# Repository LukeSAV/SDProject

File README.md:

# **SDProject**

Repo for senior design code

Link to project video: https://www.youtube.com/watch?v=O6JMgqfRybo&t=1s

## <u>Matlab</u>

Contains matlab test harness and associated files for the Extended Kalman Filter - This has since been converted to ekf_node in the ROS workspace.

## <u>SDMicro</u>

Contains all microcontroller related code for the project.

## <u>boards</u>

Contains files related to PCB design and schematics.

## <u>iOS</u>

This contains all project files related to XCode and iOS. 

##### /D2U

DeliveryInformation.swift - Singleton class used to hold relevant information to the delivery in progress.

DeliverySettingsController.swift - ViewController for the settings page. Formats and periodically updates the information on the page from FireBase.

MapMainController.swift - ViewController for the main map page. Handles map centering on desired user location and updates respective UI elements.

Waypoint.swift - Inherits MKPointAnnotation to apply color to dropped pins to distinguish between types.

## <u>ros_ws</u>

This is the ROS workspace for the project. Any packages/nodes made in ROS should be located here.

#### ROS Packages:

##### fb

This package contains the fb_node that handles interfacing to firebase. 

Nodes:

- fb_node: 
  - Publishes - /delivery_requested_status (Type: Bool)
  - Subscribes - /rtk_gpgga (Type: String)

##### rtk

This package contains the rtk_gps_node that runs code to support RTK corrections for the NS-HP-GL GPS/GNSS device. 

Nodes:

- rtk_gps_node
  - Publishes - /rtk_gpgga (Type: NavSatFix), /rtk_gpvtg (Type: HeadingSpeed)
  - Subscribes - None

##### rtk_controller

This package contains the rtk_controller node that performs path point generation to send to the microcontroller. A* algorithm, path point projection, and much more.

Nodes:

- rtk_controller_node
  - Publishes - /robot_cmd (Type: String), /next_waypoint (Type: NavSatFix), /goal_pt (Type: NavSatFix), /goal_math_pt (Type: NavSatFix)
  - Subscribes - /ekf/filtered (Type: NavSatFix), /ekf/imu/data (Type: Imu), /rtk_gpvtg (Type: String), /perception/map (Type: Image), /pitch (Type: Float32) 

##### joystick_drivers

This package contains the joy_node that interfaces the PS4 controller to ROS.

Nodes:

- joy_node: 
  - Publishes - /joy (Type: Joy)
  - Subscribes - None 

##### serial

This package contains the serial_node that handles all communication with the microcontroller.

Nodes:

- serial_node:
  - Publishes - /encoder (Type: String), /goal_string (Type: String)
  - Subscribes - /joy (Type: Joy), /delivery_requested_status (Type: Bool), /robot_cmd (Type: String)

##### perception

This package contains the lidar_node that handles creation of an obstacle map that the path planning algorithm may be run on.

Nodes:
- lidar_node:
  - Publishes - /perception/map (Type: Image)
  - Subscribes - /scan_img (Type: Image)
  
##### ekf

This package contains the ekf_node that runs the Extended Kalman Filter to fuse the robot sensor information.

Nodes:
- ekf_node:
  - Publishes - /ekf/filtered (Type: NavSatFix), /ekf/imu/data (Type: NavSatFix), /pitch (Type: Float32)
  - Subscribes - /imu/data (Type: Imu), /rtk_gpgga (Type: NavSatFix), /encoder (Type: String)

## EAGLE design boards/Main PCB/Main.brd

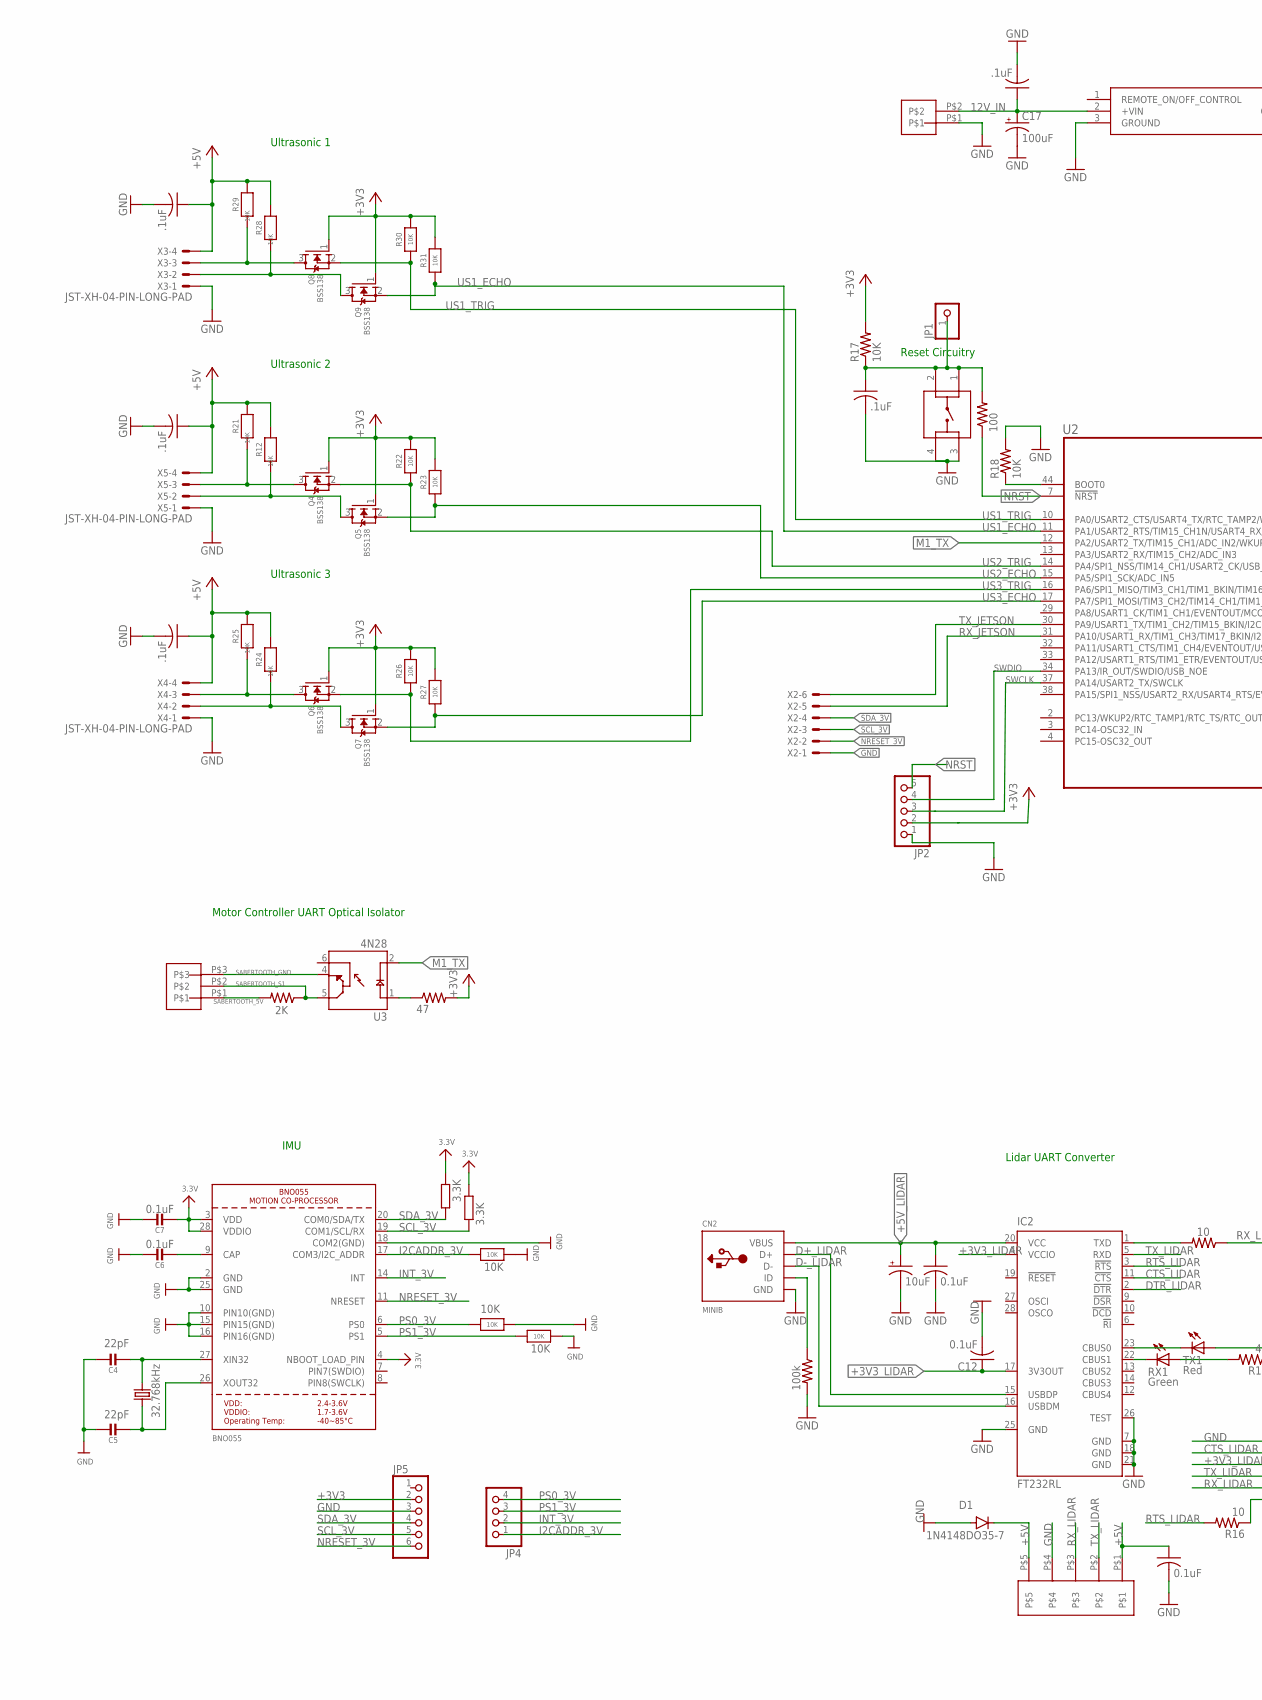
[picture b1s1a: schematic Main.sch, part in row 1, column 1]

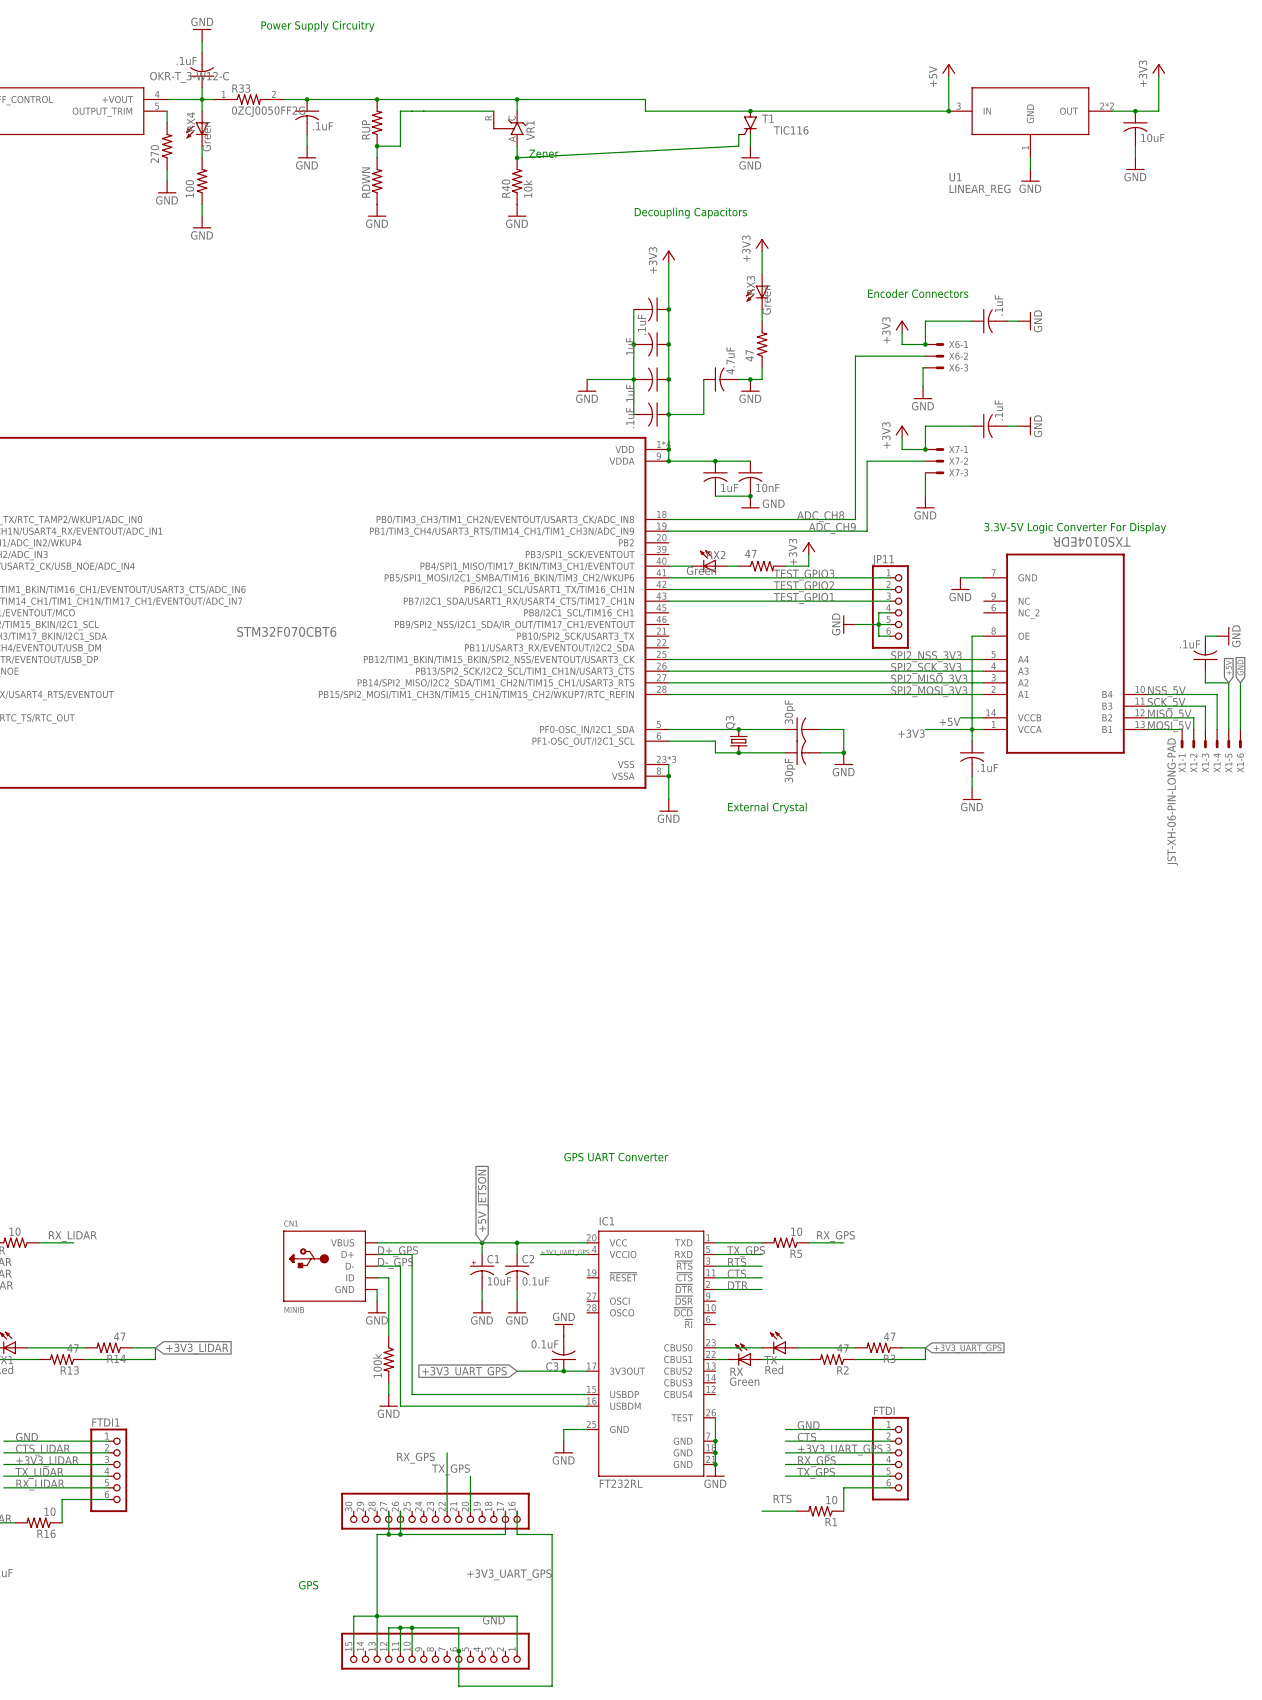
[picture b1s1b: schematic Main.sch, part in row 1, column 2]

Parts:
C1, C10: 10uF; A/3216-18R
C2, C3, C11, C12, C30: 0.1uF; C0805K
C4, C5: 22pF; 0805-NO
C6: 0.1uF; 0805-NO
C7: 0.1uF; 0805_10MGAP
C8, C13, C18, C19, C22, C23, C24, C25, C26, C27, C28, C29, C31, C32, C33: .1uF; C0805
C9: 10uF; C0805
C14, C15: 30pF; C0805
C16: 4.7uF; C0805
C17: 100uF; E2,5-7
C20: 1uF; C0805
C21: 10nF; C0805
CN1, CN2: MINIB; USB-MINIB
D1: 1N4148DO35-7; DO35-7
FTDI, FTDI1: PINHD-1X6CB; 1X06-CLEANBIG
IC1, IC2: FT232RL; SSOP28
IC4: OKR-T_3-W12-C; MURATACASEC72
J1: 3_PIN_JST-XH
J2: 2_PIN_JST-XH
J3: 5_PIN_JST-XH
JP1: PINHD-1X1; 1X01
JP2: PINHD-1X5; 1X05
JP4: HEADER-1X476MIL; 1X04_ROUND_76
JP5: MICROBUILDER_HEADER-1X676MIL; MICROBUILDER_1X06_ROUND_76
JP11: PINHD-1X6; 1X06
Q3: CRYSTALHC49S; HC49/S
Q4, Q5, Q6, Q7, Q8, Q9: BSS138; SOT23-WIDE
R1, R5, R15, R16: 10; R0805
R2, R3, R10, R11, R13, R14, R19: 47; R0805
R4, R6, R7, R22, R23, R26, R27, R30, R31: 10K; 0805-NO
R8, R9: 3.3K; R0805
R12, R21, R24, R25, R28, R29: 10K; _0805MP
R17, R18: 10K; R0805
R20: 2K; R0805
R32, R37: 100; R0805
R33: 0ZCJ0050FF2G; RESC3216X125N
R34, R35: 100k; R0805
R36: 270; R0805
R40: 10k; R0805
RDWN: R-US_R0805; R0805
RESET: TACTILE_SWITCH; SW_1825910-6-4
RUP: R-US_R0805; R0805
RX, RX1, RX2, RX3, RX4: Green; CHIP-LED0805
T1: TIC116; TO220CS
TX, TX1: Red; CHIP-LED0805
U1: LINEAR_REG; SOT223
U2: STM32F070CBT6; QFP50P900X900X160-48N
U3: 4N28; DIP880W50P254L780H450Q6
U4: TXS0104EDR; SOIC127P600X175-14N
U$1: GPS
U$3: BNO055
VR1: TL431CLP; TO92-CLP
X1, X2: JST-XH-06-PIN-LONG-PAD; JST-XH-06-PACKAGE-LONG-PAD
X3, X4, X5: JST-XH-04-PIN-LONG-PAD; JST-XH-04-PACKAGE-LONG-PAD
X6, X7: JST-XH-03-PIN-LONG-PAD; JST-XH-03-PACKAGE-LONG-PAD
Y1: 32.768kHz; CRYSTAL_8X3.8

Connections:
12V_IN: C17.+, C32.1, IC4.2 (+VIN), J2.P$2
+3V3: C7.2, C9.1, C16.1, C20.1, C21.1, C22.1, C23.1, C24.1, C25.1, C28.1, C29.1, C33.1, JP2.2, JP5.2, Q4.1 (G), Q5.1 (G), Q6.1 (G), Q7.1 (G), Q8.1 (G), Q9.1 (G), R8.2, R9.2, R10.2, R17.2, R19.2, R22.2, R23.2, R26.2, R27.2, R30.2, R31.2, RX3.A, U1.2 (OUT), U1.4 (OUT), U2.1 (VDD), U2.9 (VDDA), U2.24 (VDD), U2.36 (VDD), U2.48 (VDD), U4.1 (VCCA), U4.8 (OE), U$3.3 (VDD), U$3.4 (NBOOT_LOAD_PIN), U$3.28 (VDDIO), X6.1, X7.1; also elsewhere on the board
+3V3_LIDAR: C12.1, FTDI1.3, IC2.4 (VCCIO), IC2.17 (3V3OUT), R13.1, R14.1
+3V3_UART_GPS: C3.1, FTDI.3, IC1.4 (VCCIO), IC1.17 (3V3OUT), R2.1, R3.1, U$1.6, U$1.10, U$1.11, U$1.12, U$1.16 (1)
+5V: C8.1, C18.1, C19.1, C26.1, C27.1, C30.1, D1.C, J3.P$1, J3.P$5, R12.2, R21.2, R24.2, R25.2, R28.2, R29.2, R33.2, RUP.2, T1.A, U1.3 (IN), U4.14 (VCCB), VR1.C, X1.5, X3.4, X4.4, X5.4
+5V_JETSON: C1.+, C2.1, CN1.VBUS, IC1.20 (VCC)
+5V_LIDAR: C10.+, C11.1, CN2.VBUS, IC2.20 (VCC)
ADC_CH8: U2.18 (PB0/TIM3_CH3/TIM1_CH2N/EVENTOUT/USART3_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), X6.2
ADC_CH9: U2.19 (PB1/TIM3_CH4/USART3_RTS/TIM14_CH1/TIM1_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), X7.2
BOOT0: R18.1, U2.44 (BOOT0)
CAP: C6.2, U$3.9 (CAP); also elsewhere on the board
CTS: FTDI.2, IC1.11 (!CTS)
CTS_LIDAR: FTDI1.2, IC2.11 (!CTS)
D+_GPS: CN1.D+, IC1.15 (USBDP)
D+_LIDAR: CN2.D+, IC2.15 (USBDP)
D-_GPS: CN1.D-, IC1.16 (USBDM)
D-_LIDAR: CN2.D-, IC2.16 (USBDM)
DTR: IC1.2 (!DTR)
DTR_LIDAR: IC2.2 (!DTR)
GND: C1.-, C2.2, C3.2, C4.1, C5.1, C6.1, C7.1, C8.2, C9.2, C10.-, C11.2, C12.2, C13.2, C14.2, C15.2, C16.2, C17.-, C18.2, C19.2, C20.2, C21.2, C22.2, C23.2, C24.2, C25.2, C26.2, C27.2, C28.2, C29.2, C30.2, C31.2, C32.2, C33.2, CN1.GND, CN2.GND, D1.A, FTDI.1, FTDI1.1, IC1.7 (GND), IC1.18 (GND), IC1.21 (GND), IC1.25 (GND), IC1.26 (TEST), IC2.7 (GND), IC2.18 (GND), IC2.21 (GND), IC2.25 (GND), IC2.26 (TEST), IC4.3 (GROUND), J2.P$1, J3.P$4, JP2.1, JP5.3, JP11.4, JP11.5, JP11.6, R4.2, R6.2, R7.2, R11.1, R18.2, R32.1, R34.2, R35.2, R36.1, R40.1, RDWN.1, RESET.3, RESET.4, T1.C, U1.1 (GND), U2.8 (VSSA), U2.23 (VSS), U2.35 (VSS), U2.47 (VSS), U4.7 (GND), U$1.1, U$1.13, U$1.15, U$1.17 (2), U$1.26 (11), U$1.27 (12), U$3.2 (GND), U$3.10 (PIN10(GND)), U$3.15 (PIN15(GND)), U$3.16 (PIN16(GND)), U$3.18 (COM2(GND)), U$3.25 (GND), X1.6, X2.1, X3.1, X4.1, X5.1, X6.3, X7.3; also elsewhere on the board
I2CADDR_3V: JP4.1, R7.1, U$3.17 (COM3/I2C_ADDR); also elsewhere on the board
INT_3V: JP4.2, U$3.14 (INT); also elsewhere on the board
LED: RX2.C, U2.40 (PB4/SPI1_MISO/TIM17_BKIN/TIM3_CH1/EVENT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)
M1_TX: U2.12 (PA2/USART2_TX/TIM15_CH1/ADC_IN2/WKUP4), U3.2 (C_D)
MISO_5V: U4.12 (B2), X1.2
MOSI_5V: U4.13 (B1), X1.1
unnamed 26: C4.2, U$3.27 (XIN32), Y1.P$4 (2); also elsewhere on the board
unnamed: FTDI.6, R1.1
unnamed: R10.1, RX2.A
unnamed: R11.2, RX3.C
unnamed: IC1.1 (TXD), R5.2
unnamed: IC1.23 (CBUS0), TX.C
unnamed: IC1.22 (CBUS1), RX.C
unnamed: R2.2, RX.A
unnamed: R3.2, TX.A
unnamed 35: C5.2, U$3.26 (XOUT32), Y1.P$1 (1); also elsewhere on the board
unnamed: CN2.ID, R34.1
unnamed: R32.2, RX4.C
unnamed: CN1.ID, R35.1
unnamed: IC2.23 (CBUS0), TX1.C
unnamed: IC2.22 (CBUS1), RX1.C
unnamed: R13.2, RX1.A
unnamed: R14.2, TX1.A
unnamed: IC2.1 (TXD), R15.2
unnamed: FTDI1.6, R16.1
unnamed: IC4.5 (OUTPUT_TRIM), R36.2
unnamed: C31.1, IC4.4 (+VOUT), R33.1, RX4.A
unnamed: Q4.3 (D), R21.1, X5.3
unnamed: Q5.3 (D), R12.1, X5.2
unnamed: R40.2, T1.G, VR1.A
unnamed: RDWN.2, RUP.1, VR1.R
unnamed: Q6.3 (D), R25.1, X4.3
unnamed: Q7.3 (D), R24.1, X4.2
unnamed: R19.1, U3.1 (A_D)
unnamed: C14.1, Q3.2, U2.5 (PF0-OSC_IN/I2C1_SDA)
unnamed: C15.1, Q3.1, U2.6 (PF1-OSC_OUT/I2C1_SCL)
unnamed: Q8.3 (D), R29.1, X3.3
unnamed: Q9.3 (D), R28.1, X3.2
NRESET_3V: JP5.6, U$3.11 (NRESET), X2.2; also elsewhere on the board
NRST: JP2.5, R37.1, U2.7 (!NRST)
NSS_5V: U4.10 (B4), X1.4
PS0_3V: JP4.4, R4.1, U$3.6 (PS0); also elsewhere on the board
PS1_3V: JP4.3, R6.1, U$3.5 (PS1); also elsewhere on the board
RESET: C13.1, JP1.1, R17.1, R37.2, RESET.1, RESET.2
RTS: IC1.3 (!RTS), R1.2
RTS_LIDAR: IC2.3 (!RTS), R16.2
RX_GPS: FTDI.4, R5.1, U$1.22 (7)
RX_JETSON: U2.31 (PA10/USART1_RX/TIM1_CH3/TIM17_BKIN/I2C1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), X2.5
RX_LIDAR: FTDI1.5, J3.P$3, R15.1
SABERTOOTH_5V: J1.P$1, R20.2
SABERTOOTH_GND: J1.P$3, U3.4 (E_T)
SABERTOOTH_S1: J1.P$2, R20.1, U3.5 (C_T)
SCK_5V: U4.11 (B3), X1.3
SCL_3V: JP5.5, R9.1, U$3.19 (COM1/SCL/RX), X2.3; also elsewhere on the board
SDA_3V: JP5.4, R8.1, U$3.20 (COM0/SDA/TX), X2.4; also elsewhere on the board
SPI2_MISO_3V3: U2.27 (PB14/SPI2_MISO/I2C2_SDA/TIM1_CH2N/TIM15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), U4.3 (A2)
SPI2_MOSI_3V3: U2.28 (PB15/SPI2_MOSI/TIM1_CH3N/TIM15_CH1N/TIM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), U4.2 (A1)
SPI2_NSS_3V3: U2.25 (PB12/TIM1_BKIN/TIM15_BKIN/SPI2_NSS/EVEN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), U4.5 (A4)
SPI2_SCK_3V3: U2.26 (PB13/SPI2_SCK/I2C2_SCL/TIM1_CH1N/USART3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), U4.4 (A3)
SWCLK: JP2.3, U2.37 (PA14/USART2_TX/SWCLK)
SWDIO: JP2.4, U2.34 (PA13/IR_OUT/SWDIO/USB_NOE)
TEST_GPIO1: JP11.3, U2.43 (PB7/I2C1_SDA/USART1_RX/USART4_CTS/TIM17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)
TEST_GPIO2: JP11.2, U2.42 (PB6/I2C1_SCL/USART1_TX/TIM16_CH1N)
TEST_GPIO3: JP11.1, U2.41 (PB5/SPI1_MOSI/I2C1_SMBA/TIM16_BKIN/TIM3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)
TX_GPS: FTDI.5, IC1.5 (RXD), U$1.20 (5)
TX_JETSON: U2.30 (PA9/USART1_TX/TIM1_CH2/TIM15_BKIN/I2C1_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), X2.6
TX_LIDAR: FTDI1.4, IC2.5 (RXD), J3.P$2
US1_ECHO: Q9.2 (S), R31.1, U2.11 (PA1/USART2_RTS/TIM15_CH1N/USART4_RX/EVE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)
US1_TRIG: Q8.2 (S), R30.1, U2.10 (PA0/USART2_CTS/USART4_TX/RTC_TAMP2/WKUP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)
US2_ECHO: Q5.2 (S), R23.1, U2.15 (PA5/SPI1_SCK/ADC_IN5)
US2_TRIG: Q4.2 (S), R22.1, U2.14 (PA4/SPI1_NSS/TIM14_CH1/USART2_CK/USB_NO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)
US3_ECHO: Q7.2 (S), R27.1, U2.17 (PA7/SPI1_MOSI/TIM3_CH2/TIM14_CH1/TIM1_C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)
US3_TRIG: Q6.2 (S), R26.1, U2.16 (PA6/SPI1_MISO/TIM3_CH1/TIM1_BKIN/TIM16_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)

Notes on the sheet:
Power Supply Circuitry
GPS
GPS UART Converter
Ultrasonic 1
Ultrasonic 2
Ultrasonic 3
Motor Controller UART Optical Isolator
IMU
Lidar UART Converter
Reset Circuitry
External Crystal
3.3V-5V Logic Converter For Display
Encoder Connectors
Decoupling Capacitors
10K
Zener

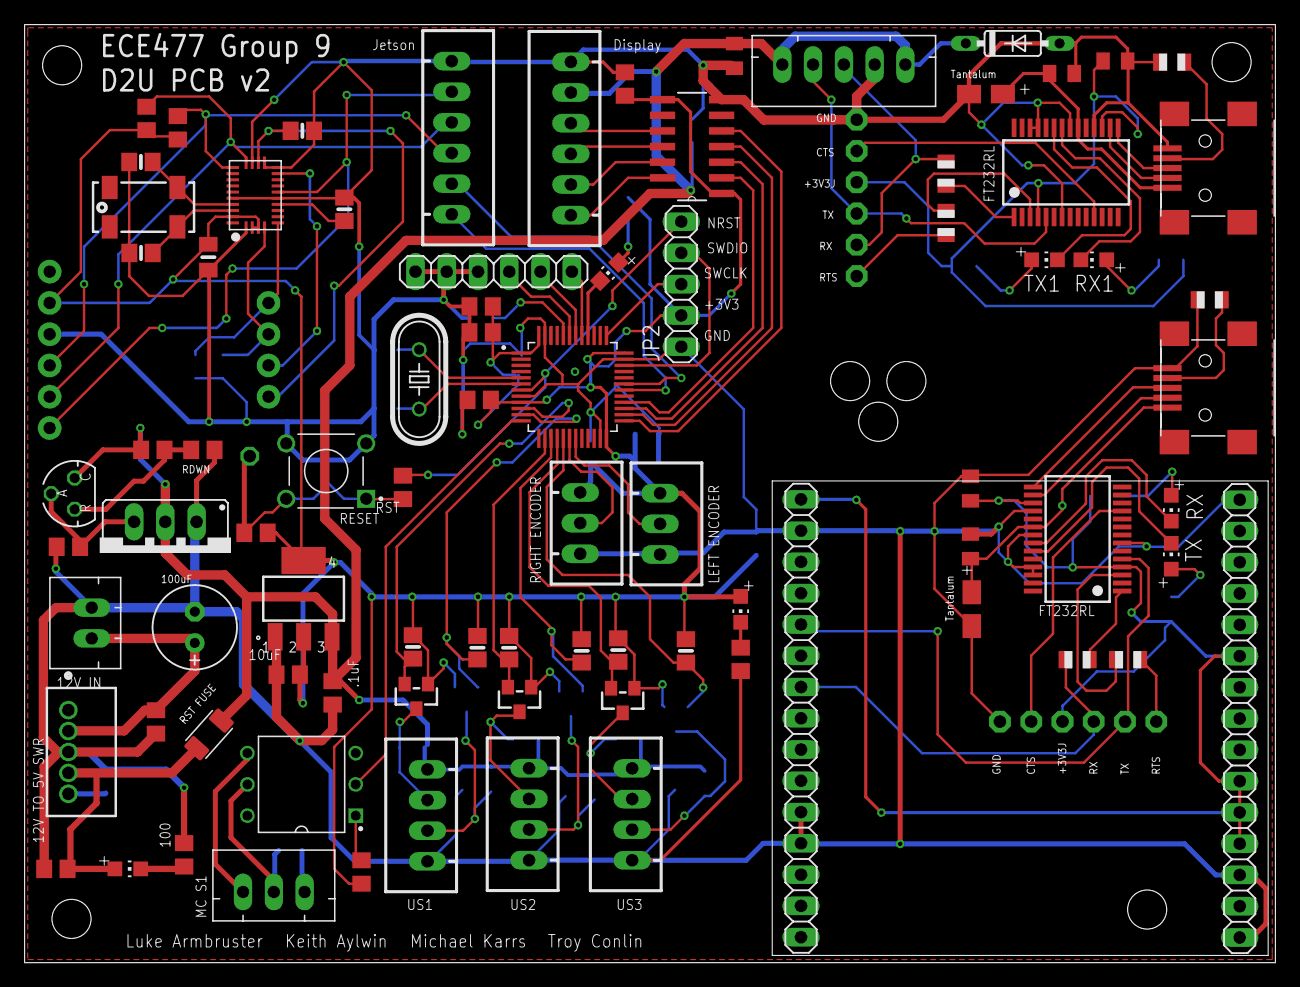
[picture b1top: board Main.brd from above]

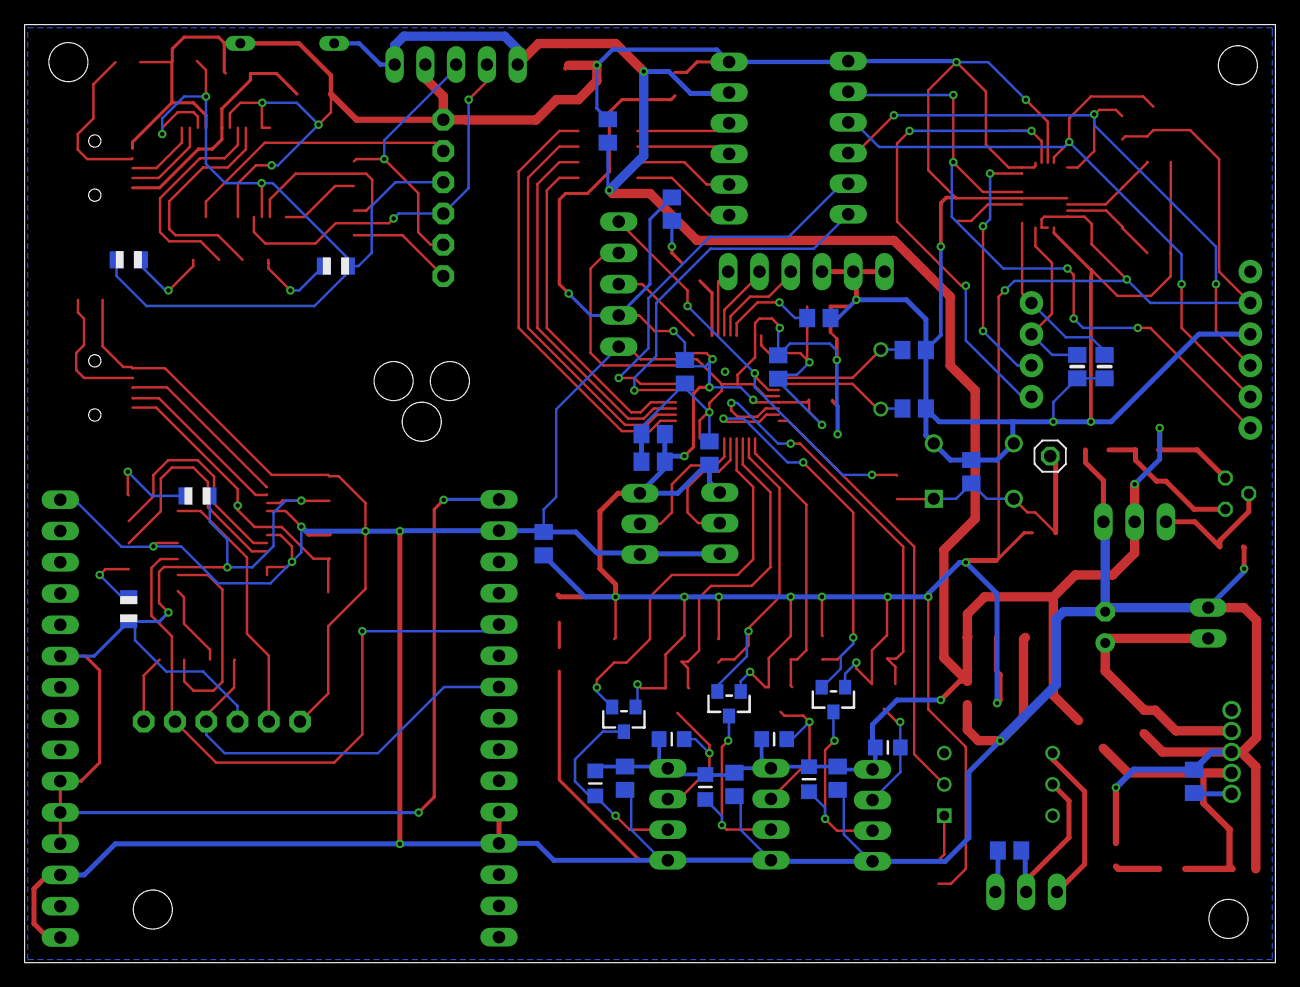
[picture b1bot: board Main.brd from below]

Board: 2 copper layers, 101.6 x 76.2 mm, 120 parts (33 on the bottom side), 91 nets.

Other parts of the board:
U$9: MICROBUILDER_BNO055

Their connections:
+3V3: U$9.3, U$9.4, U$9.28; also elsewhere on the board
CAP: U$9.9; also elsewhere on the board
GND: U$9.2, U$9.10, U$9.15, U$9.16, U$9.18, U$9.25; also elsewhere on the board
I2CADDR_3V: U$9.17; also elsewhere on the board
INT_3V: U$9.14; also elsewhere on the board
unnamed 26: U$9.27; also elsewhere on the board
unnamed 35: U$9.26; also elsewhere on the board
NRESET_3V: U$9.11; also elsewhere on the board
PS0_3V: U$9.6; also elsewhere on the board
PS1_3V: U$9.5; also elsewhere on the board
SCL_3V: U$9.19; also elsewhere on the board
SDA_3V: U$9.20; also elsewhere on the board

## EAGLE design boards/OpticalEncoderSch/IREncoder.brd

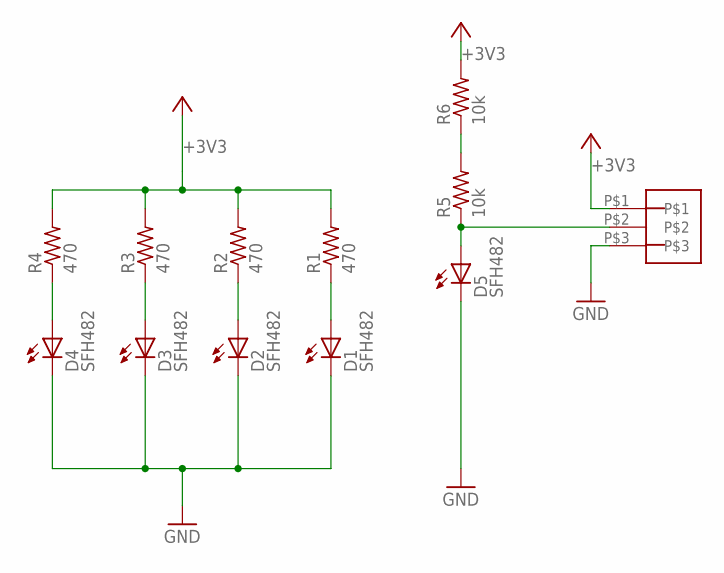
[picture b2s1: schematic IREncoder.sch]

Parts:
D1, D2, D3, D4, D5: SFH482
J1: 3_PIN_JST-XH
R1, R2, R3, R4: 470; R0805
R5, R6: 10k; R0805

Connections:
+3V3: J1.P$1, R1.2, R2.2, R3.2, R4.2, R6.2
GND: D1.K (C), D2.K (C), D3.K (C), D4.K (C), D5.K (C), J1.P$3
unnamed: D4.A, R4.1
unnamed: D3.A, R3.1
unnamed: D2.A, R2.1
unnamed: D1.A, R1.1
unnamed: D5.A, J1.P$2, R5.1
unnamed: R5.2, R6.1

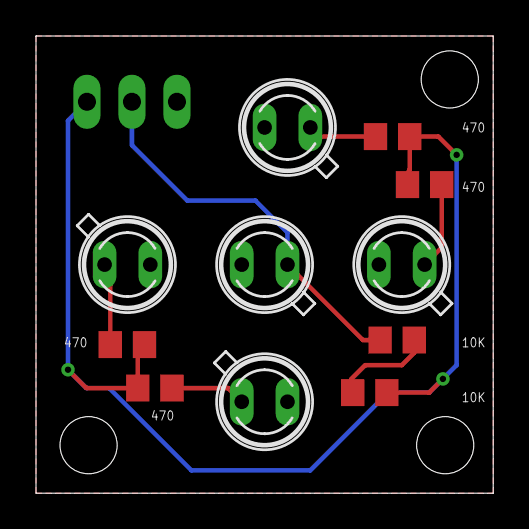
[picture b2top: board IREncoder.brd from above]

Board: 2 copper layers, 25.4 x 25.4 mm, 12 parts (1 on the bottom side), 8 nets.

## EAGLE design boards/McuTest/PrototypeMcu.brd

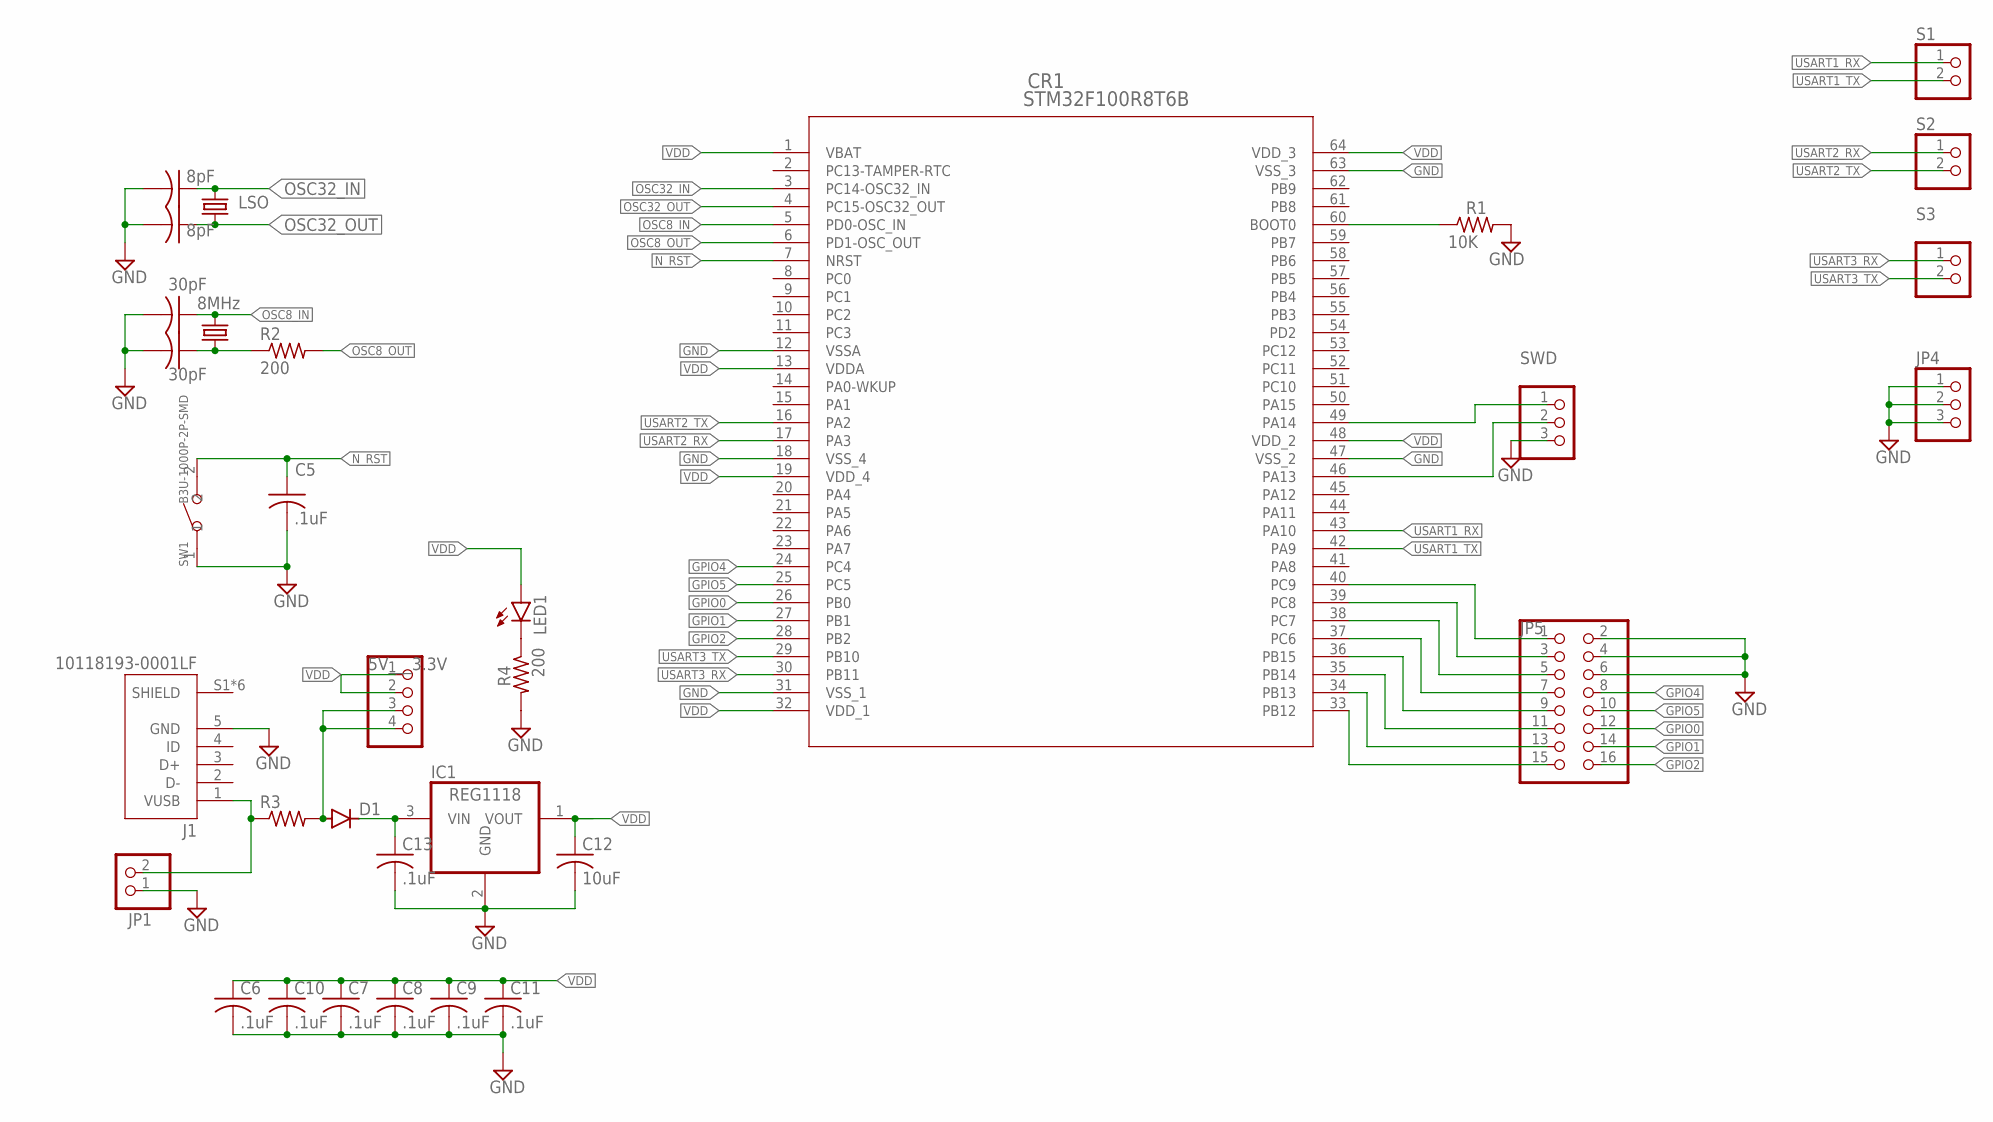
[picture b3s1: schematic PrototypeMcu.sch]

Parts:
5V___3.3V: PINHD-1X4; 1X04
C1, C2: 8pF; C0402
C3, C4: 30pF; C0402
C5, C6, C7, C8, C9, C10, C11, C13: .1uF; C0402
C12: 10uF; C0402
CR1: STM32F100R8T6B; LQFP-64
D1: DIODE-SOD57-10; SOD57-10
IC1: REG1118; SOT223
J1: 10118193-0001LF; FCI_10118193-0001LF
JP1: PINHD-1X2; 1X02
JP4: PINHD-1X3; 1X03
JP5: PINHD-2X8; 2X08
LED1: LEDCHIPLED_0603; CHIPLED_0603
LSO: CRYSTALTC26V; TC26V
Q1: 8MHz; HC49/S
R1: 10K; R0402
R2, R4: 200; R0402
R3: R-US_M1206; M1206
S1, S2, S3: PINHD-1X2; 1X02
SW1: B3U-1000P-2P-SMD; SW2-2.6-3.0X2.5X1.2+0.4MM
SWD: PINHD-1X3; 1X03

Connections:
GND: C1.2, C2.2, C3.2, C4.2, C5.2, C6.2, C7.2, C8.2, C9.2, C10.2, C11.2, C12.2, C13.2, CR1.12 (VSSA), CR1.18 (VSS_4), CR1.31 (VSS_1), CR1.47 (VSS_2), CR1.63 (VSS_3), IC1.2 (GND), J1.5 (GND), JP1.1, JP4.1, JP4.2, JP4.3, JP5.2, JP5.4, JP5.6, R1.2, R4.2, SW1.1, SWD.3
GPIO0: CR1.26 (PB0), JP5.12
GPIO1: CR1.27 (PB1), JP5.14
GPIO2: CR1.28 (PB2), JP5.16
GPIO4: CR1.24 (PC4), JP5.8
GPIO5: CR1.25 (PC5), JP5.10
unnamed: CR1.60 (BOOT0), R1.1
unnamed: C13.1, D1.C, IC1.3 (VIN)
unnamed: CR1.40 (PC9), JP5.1
unnamed: 5V___3.3V.3, 5V___3.3V.4, D1.A, R3.2
unnamed: C4.1, Q1.2, R2.1
unnamed: CR1.46 (PA13), SWD.2
unnamed: CR1.39 (PC8), JP5.3
unnamed: CR1.49 (PA14), SWD.1
unnamed: CR1.38 (PC7), JP5.5
unnamed: CR1.37 (PC6), JP5.7
unnamed: CR1.36 (PB15), JP5.9
unnamed: CR1.35 (PB14), JP5.11
unnamed: CR1.34 (PB13), JP5.13
unnamed: CR1.33 (PB12), JP5.15
unnamed: LED1.C, R4.1
unnamed: J1.1 (VUSB), JP1.2, R3.1
N_RST: C5.1, CR1.7 (NRST), SW1.2
OSC8_IN: C3.1, CR1.5 (PD0-OSC_IN), Q1.1
OSC8_OUT: CR1.6 (PD1-OSC_OUT), R2.2
OSC32_IN: C1.1, CR1.3 (PC14-OSC32_IN), LSO.2
OSC32_OUT: C2.1, CR1.4 (PC15-OSC32_OUT), LSO.1
USART1_RX: CR1.43 (PA10), S1.1
USART1_TX: CR1.42 (PA9), S1.2
USART2_RX: CR1.17 (PA3), S2.1
USART2_TX: CR1.16 (PA2), S2.2
USART3_RX: CR1.30 (PB11), S3.1
USART3_TX: CR1.29 (PB10), S3.2
VDD: 5V___3.3V.1, 5V___3.3V.2, C6.1, C7.1, C8.1, C9.1, C10.1, C11.1, C12.1, CR1.1 (VBAT), CR1.13 (VDDA), CR1.19 (VDD_4), CR1.32 (VDD_1), CR1.48 (VDD_2), CR1.64 (VDD_3), IC1.1 (VOUT), LED1.A

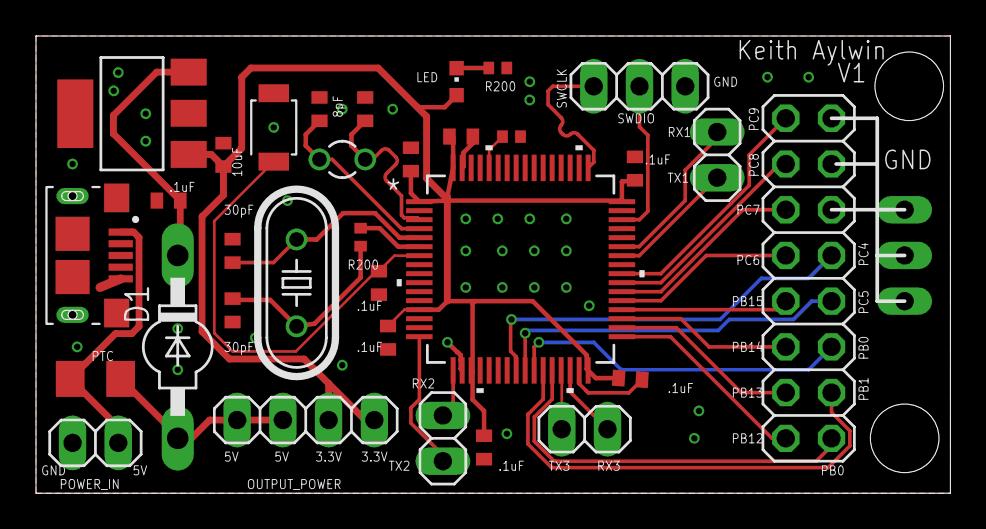
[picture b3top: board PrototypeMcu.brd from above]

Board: 2 copper layers, 50.8 x 25.4 mm, 33 parts (1 on the bottom side), 34 nets.

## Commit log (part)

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2016-02-11 Fixing serial transmission to micro
2016-02-11 Serial Manager
2018-01-28 Fixed formatting in landscape mode for main storyboard
2018-02-03 Added motor controls for left/right buttons
2018-02-07 Added serial output from bluetooth to control motor wheels
2018-02-10 Restructured source into IOS and BluetoothTuner. Added useful.gitignore
2018-02-10 Added support for receiving instructions to arduino module
2018-02-10 Added new self balancing file
2018-02-11 Added balance desktop and began merging code
2018-03-25 Added shorter bounds to slider controls
2018-03-25 Added support for Pods'
2018-03-27 Added joystick controller to move robot and stop button
2018-03-29 Added functionality for watchOS. Sends sync pulses now to tell the Arduino it is still connected.
2018-03-29 Fixed Luke's broken code for phone app
2018-04-02 Fixed timer continuing when going back from second controller to first
2018-04-19 Added images and modifications to phone app
2018-04-19 Adding the motor controller source
2018-09-22 Initializing for ground plane detection
2018-12-23 Updating to working iOS application
2018-12-31 Created initial board schematic
2018-12-31 All wires traced but ground plane is not complete
2018-12-31 Design rules check out
2018-12-31 Added a fuse and impedance matched clock signals
2018-12-31 LED and silkscreen Aded
2019-01-01 Order placed to OSH Park
2019-01-03 Updated RTK code to work on Jetson over single USB connection and publish GPS position.
2019-01-04 Cleaning up directory and updating gitignore
2019-01-04 Changes to icon sets and implementation of core functionality to app navigation.
2019-01-04 Updating UI
2019-01-04 Add files via upload
    Adding readme file with skeleton format and updates on what I've worked on so far.
2019-01-06 Updating UI elements and adding support for pin following user/robot locations. Cleaned up firebase code
2019-01-07 Updating class structure to support nearest landmark/path detection
2019-01-08 Adding nearest landmark feature and cleaning up class for defined robot paths
2019-01-08 Adding joystick files
2019-01-09 "added Libraries for JST connectors"
2019-01-10 Optical Encoder PCB updates. Awaits peer review and shipment
2019-01-11 Adding to package to subscribe to joystick output
2019-01-11 Adding serial capability
2019-01-16 Fixed issue in ntrip client where caster disconnects and doesn't recover. Added controller package to handle basic navigation
2019-01-17 Moved waypoint/landmark calculations out of the ntrip client and started functionality to support GPS driven navigation
2019-01-18 Adding some basic logic to GPS controller
2019-01-21 Updating firebase manager to push more info for phone app use
2019-01-21 Removing unnecessary joystick driver causing problems on lubuntu for rPi
2019-01-24 Formatting fixes
2019-01-24 Fixing rc_manager and pushing latest iOS code
2019-01-26 Adding UART receive interrupts for the micro project.
2019-01-27 Adding proper interrupts for UART tx/rx
2019-01-27 Adding readme
2019-01-29 Beginning support for ultrasonic interrupts
2019-02-02 Fixing rc callback
2019-02-03 Adjusting voltage range for encoders
2019-02-03 Removing unnecessary serial write from rtk manager
2019-02-03 Cleaned up old, dead projects
2019-02-03 Added the gps generator to check EKF
2019-02-03 Fixed Q matrix
2019-02-03 Updating main launch file
2019-02-03 Added rplidar
2019-02-06 Library with IMU parts footprint
2019-02-06 Adding USB to UART schematic and library
2019-02-07 Adding PCB with UART converter components
2019-02-07 Adding better UART breakout board
2019-02-07 Adding miniusb UART converter and updating main to include IMU
2019-02-07 Cleaning up PCB folders aand updating proper dimensioned GPS chip
2019-02-08 Updating microcontroller code to enable ultrasonics
2019-02-08 Updating boaard file and removing settings from git
2019-02-08 Fixing mirrored FTDI on reverse of board
2019-02-09 Updating for packetized serial mode on motor controller
2019-02-10 UART for packetized mode on motor controller now working
2019-02-10 Updating drive function
2019-02-10 Updating parts library for IMU
2019-02-12 Merged libraries
2019-02-13 Updated microcontroller code with SPI interface
2019-02-13 Making separate package for serial comms and adding path planning package
2019-02-15 Adding microcontroller to project
2019-02-15 Connected JSTs and arranged them in schematic
2019-02-16 First major layout session. Fixed up wanrings in GPS_UART module in the sensor module, and in the microcontroller module
2019-02-16 Continued finishing the Schematic for the board
2019-02-16 Cleaning up UART converter schematic
2019-02-16 Initial layout of main components
2019-02-17 Cleaning up layout on main PCB
2019-02-17 Further improvements on main PCB
2019-02-17 Routed power, routed encoders, routed ultrasonics, and logic level converters
2019-02-18 Completed routing and awaiting review
2019-02-18 Cleaned up ground trace
2019-02-18 Fixed board to adhere to DRC's and fixed schematic to adhere to ERC's
2019-02-18 Increasing +3V3 width to micro
2019-02-19 Moved two vias
2019-02-19 Latest micro code
2019-02-19 Routed decoupling caps closer to micro and added vias for extra GPIO
2019-02-20 Adding CAAM outputs
2019-02-20 Added equations to generate path from two wheel positions
2019-02-20 Fixing board routing and adding reset pin per Todd's suggestions
2019-02-20 Routed headers for IMU backup
2019-02-21 Fixing IMU traces and adding descriptive net names
2019-02-21 More routing and naming improvements
2019-02-21 Minor routing improvements and net naming
2019-02-21 More improvements on trace widths, orientations
2019-02-22 Minor routing fixes
2019-02-22 Added pullup resistors for SDA and SCL
2019-02-23 Added indicator LEDs to board and cleaned up iOS assets
2019-02-23 Cleaning up routing and labels for design review
2019-02-24 Added a resettable fuse to the boards
2019-02-25 Moving labels to correct layer for silkscreen and added a view more descriptive labels
2019-02-25 Added ground planes to top and bottom for ordering
2019-02-25 Updating board number and silkscreen layers for second order
2019-02-26 Updating README to reflect current ROS workspace state
2019-02-26 Improvements to the rtk client, controller, and firebase manager. Using NavSatFix for GPGGA message and custom message for GPVTG message
2019-02-27 Adding diode for lidar protection
2019-02-27 More trace cleanup
2019-02-27 Fixing ground trace width
2019-02-27 Fixing trace widths and net names
2019-02-27 Fixing trace angle to ADC power
2019-02-27 AAdding decoupling capacitors for design review
2019-02-28 Fixed motor controller circuit
2019-02-28 Fixing trace width on sabertooth ground
2019-02-28 Increased trace width and added backup switching regulator support circuitry
2019-03-01 Fixing GPIO pin bank
2019-03-01 More luke changes
2019-03-02 Finished moving encoders and reset pin
2019-03-02 Minor spacing changes
2019-03-02 Fixing logic converter circuit
2019-03-03 Connecting 5V line for display IC
2019-03-04 Moving some traces for final design
2019-03-05 Routed crowbar circuit
2019-03-05 Minor trace routing changes
2019-03-05 Moving a couple traces close to pads
2019-03-05 Updating with latest PCB submission
2019-03-10 Test serial functionality
2019-03-11 Improving A* search
2019-03-14 Adding BNO055 imu driver
2019-03-14 Added package for EKF
2019-03-19 UI improvements to iOS application
2019-03-22 Integrating local and global navigation
2019-03-27 adding IMU driver and updating serial manager for jetson
2019-03-29 EKF Python files
2019-03-29 Fixing UART communication logic
2019-03-29 Added perception node
2019-03-30 Added a structure to the ekf node
2019-03-30 Removed swap files from git ignore
2019-03-31 Some fixes to USART comms to Jetson
2019-03-31 Making further improvements to the microcontroller code
2019-04-01 Updating main.launch file and adding serial hotfixes
2019-04-01 Fixing serial timeout and adding firebase module to launch file
2019-04-01 Fixing main to reduce ultrasonic polling cost and increasing baud rate between Jetson and micro
2019-04-01 Updating to support multithreaded NTRIP service
2019-04-03 udpated ekf_node part 2
2019-04-03 Adding code to move the robot in a straight line using encoders only
2019-04-03 Working on Ekf_node
2019-04-03 EKF Updates
2019-04-03 Ekf modifications
2019-04-05 Integrating control planning into microcontroller source
2019-04-05 Debug changes to the control algorithm
2019-04-06 Updating control algorithm
2019-04-06 Changes to pointupdate function
2019-04-07 More fixes to control algorithm
2019-04-07 Further updating control algorithm
2019-04-07 Enabling control algorithm
2019-04-07 EKF Node
2019-04-10 latest ekf_node
2019-04-11 Made modifications to support waypoint navigation - still need to update and send points
2019-04-11 Fixing initial EKF heading and broadcasting points for control algorithm
2019-04-12 Updating serial manager to support sending points to microcontroller
2019-04-12 Fixing merge conflicts
2019-04-13 Changes made while testing
2019-04-13 Updating remainder of points on the MSEE to Hovde route
2019-04-13 Testing changes
2019-04-13 Updating control algorithm to improve performance on grades
2019-04-13 Added support for reading goal point data, added support for plotting goal point data
2019-04-13 Fixing string formatting
2019-04-14 Created file to display goal points
2019-04-14 Merging path planning with rtk_controller and getting waypoint intersection with grid edge
2019-04-14 Fixing issues with object avoidance map
2019-04-15 Updating rtk_controller to ignore lidar data for now
2019-04-15 Minor fixes to obstacle avoidance code
2019-04-16 Added path traceback with A* in addition to linear interpolation for testing
2019-04-16 Fixed a slope calculation and removed some hairy logic
2019-04-16 SetMotors2
2019-04-17 Updating on the fly changes
2019-04-17 Adding on the fly changes during testing
2019-04-17 Broken calculations for waypoint navigation
2019-04-17 almost
2019-04-17 New towards and away logic
2019-04-17 Nearly working path point projection
2019-04-17 Fixing angle
2019-04-17 Updating with mikes fixes
2019-04-17 EKF changes
2019-04-17 Further EKF changes
2019-04-17 Unfucking EKF stuff
2019-04-18 Updating things to make startup script work
2019-04-18 Adding option to use old way of navigating waypoints
2019-04-19 Adding perception to launch file
2019-04-19 Switching to straight waypoint following
2019-04-20 On the fly changes to motor controller algo
2019-04-20 Adding updated PI code
2019-04-20 Updating PI controller
2019-04-20 Updated PI controller
2019-04-20 Added a sample proportional-integral controller
2019-04-21 Added WheelControl function
2019-04-21 On the fly changes to PiControl
2019-04-21 More changes outside
2019-04-21 Overshoot changes
2019-04-21 Changes while working outside
2019-04-22 Adding proportional controller to test tomorrow
2019-04-22 Updating my proportional controller
2019-04-22 Parameter changes
2019-04-22 Parameter changes to function today
2019-04-22 Working changes in lab
2019-04-22 test set motors
2019-04-23 changes to SetMotors3
2019-04-23 Changes to PIMotors
2019-04-23 changed heading logic
2019-04-23 Updating with outdoor test
2019-04-23 Reasonable proportional controller
2019-04-23 Initial pid controller
2019-04-23 Adding second set of map points between the EE bike path and MSEE
2019-04-23 Added braking in the case it gets out of control
2019-04-23 Keith's shitty code
2019-04-23 Encoder bandaid
2019-04-23 remove encoder bandaid
2019-04-24 On the fly changes to miro code
2019-04-24 new robot_cmd points to Jetson
2019-04-24 Added an imu pitch publisher to the ekf_node
2019-04-24 tired
2019-04-24 publish waypoint data for visualization
2019-04-24 Mike's experimental code
2019-04-24 finished adding mike experimental code
2019-04-24 Keith's algo
2019-04-24 Fixing micro merge
2019-04-24 Adding callback for pitch message
2019-04-24 Added pitch
2019-04-24 Uncomented waypoint code to micro
2019-04-24 Fixed/Broke some stuff
2019-04-24 Adding e stop
2019-05-03 Added doxygen style comments to the ros workspace
2019-05-03 Updating some ROS stuff in README
2019-05-03 Updated README include all ROS pub/sub messages and types
2019-05-03 Create LICENSE
2019-05-03 Removing temp files
2020-11-18 Add CAD Screenshots

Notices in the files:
parts and their libraries:
microbuilder: This work is placed in the public domain, and may be freely used for commercial and non-commercial work with the following conditions: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
